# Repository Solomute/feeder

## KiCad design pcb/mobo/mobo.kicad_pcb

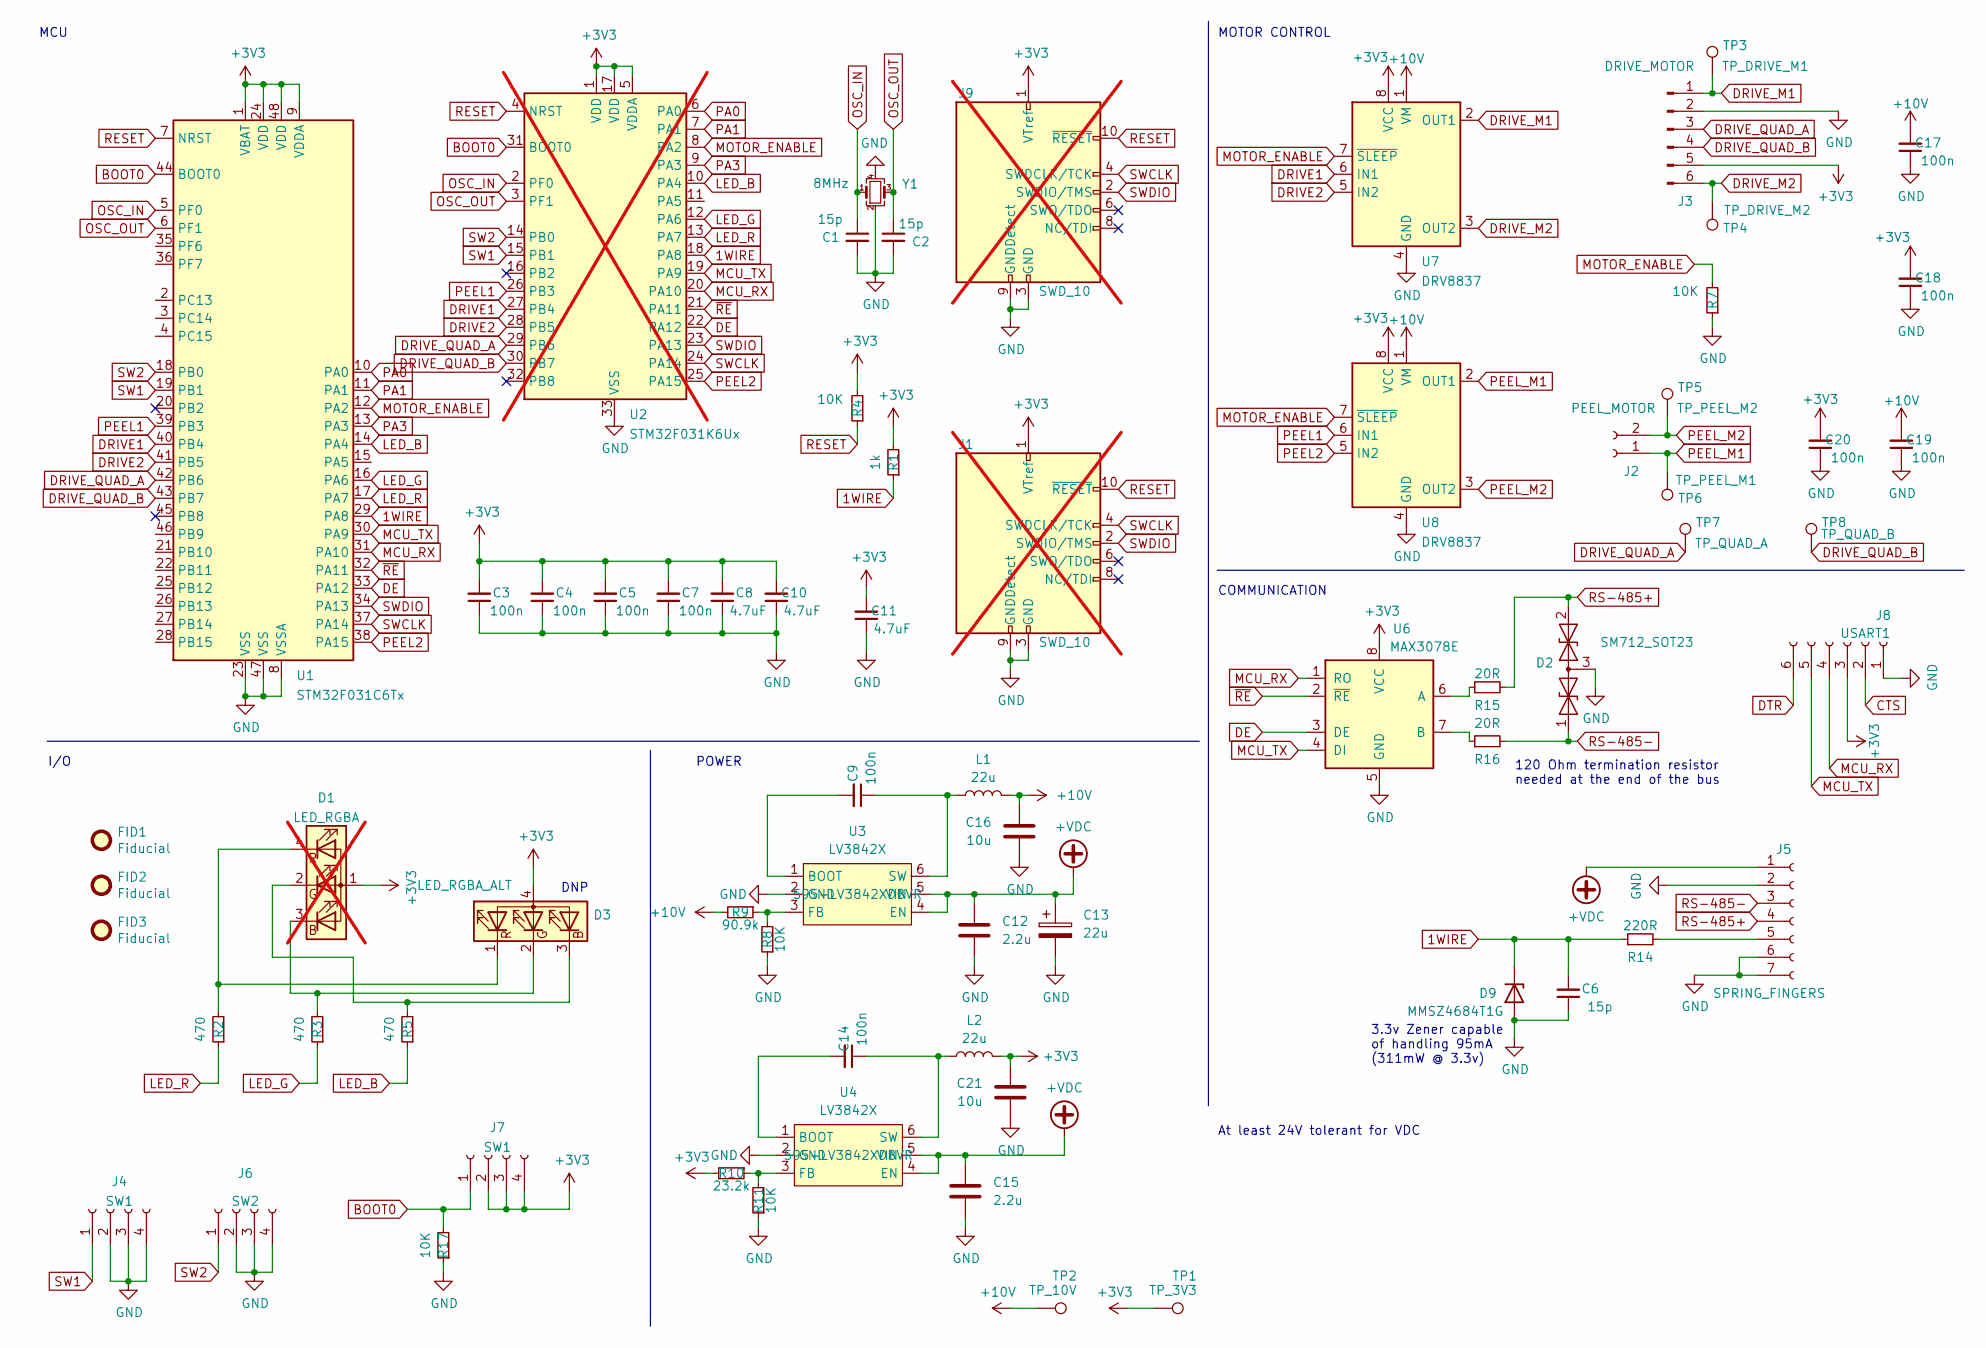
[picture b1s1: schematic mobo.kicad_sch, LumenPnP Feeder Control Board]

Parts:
C1, C2: 15p; C_0805_2012Metric; Mouser Part Number 603-CC805JRNPO9BN150; JLCPCB C1794
C3, C4, C5, C7, C9, C14, C17, C18, C19, C20: 100n; C_0805_2012Metric; Mouser Part Number 791-0805B104K500CT; JLCPCB C49678
C6: 15p; C_0805_2012Metric; Mouser Part Number 603-CC805JRNPO9BN150; JLCPCB C49678
C8, C10, C11: 4.7uF; C_0805_2012Metric; Mouser Part Number 187-CL21A475KPFNNNG; JLCPCB C49678
C12, C15: 2.2u; C_0805_2012Metric; Mouser Part Number 963-UMK212ABJ225KG-T
C13: 22u; CP_Elec_5x5.3; Mouser Part Number 80-EDK226M035A9DAA
C16, C21: 10u; C_0805_2012Metric; Mouser Part Number 187-CL21A106KOQNNNE
D1: LED_RGBA; MHS110FRGBCT; not fitted
D2: SM712_SOT23; SOT-23; Mouser Part Number 576-SM712-02HTG; LCSC C521963
D3: LED_RGBA_ALT; LED_LiteOn_LTST-C19HE1WT; Mouser Part Number 859-LTSTC19HE1WTRS1
D9: MMSZ4684T1G; D_SOD-123; Mouser Part Number 863-MMSZ4684T1G; JLCPCB MMSZ4684T1G
FID1, FID2, FID3: Fiducial; Fiducial_1mm_Mask2mm
J1: SWD_10; PinHeader_2x05_P1.27mm_Vertical_SMD; not fitted
J2: PEEL_MOTOR; Molex_PicoBlade_53261-0271_1x02-1MP_P1.25mm_Horizontal; Mouser Part Number 538-53261-0271; LCSC C2845379
J3: DRIVE_MOTOR; Molex_PicoBlade_53261-0671_1x06-1MP_P1.25mm_Horizontal; Mouser Part Number 538-53261-0671; LCSC C2845383
J4, J7: SW1; 1TS003B-1400-3500A-CT; Mouser Part Number 179-TS314635B260RASM; LCSC C319392
J5: SPRING_FINGERS; AVX-9155-005-541; Mouser Part Number 581-009155005541006
J6: SW2; 1TS003B-1400-3500A-CT; Mouser Part Number 179-TS314635B260RASM; LCSC C319392
J8: USART1; UART_FRICTION_FIT
J9: SWD_10; SWD-No-Paste; not fitted
L1, L2: 22u; L_4018; Mouser Part Number 963-NRS4018T220MDGJV
R1: 1k; R_0805_2012Metric; Mouser Part Number 708-RMCF0805FG1K00; JLCPCB C17513
R2, R3, R5: 470; R_0805_2012Metric; Mouser Part Number 603-RC0805JR-10470RL; JLCPCB C17710
R4, R7, R8, R11, R17: 10K; R_0805_2012Metric; Mouser Part Number 603-RE0805FRE0710KL; JLCPCB C17513
R9: 90.9k; R_0805_2012Metric; Mouser Part Number 71-CRCW0805-90.9K-E3
R10: 23.2k; R_0805_2012Metric; Mouser Part Number 603-RC0805FR-0723K2L
R14: 220R; R_0805_2012Metric; Mouser Part Number 667-ERJ-P06J221V
R15, R16: 20R; R_0805_2012Metric; Mouser Part Number 660-RK73H2ATTDD20R0F
TP1: TP_3V3; TestPoint_Pad_D2.0mm
TP2: TP_10V; TestPoint_Pad_D2.0mm
TP3: TP_DRIVE_M1; TestPoint_Pad_D2.0mm
TP4: TP_DRIVE_M2; TestPoint_Pad_D2.0mm
TP5: TP_PEEL_M2; TestPoint_Pad_D2.0mm
TP6: TP_PEEL_M1; TestPoint_Pad_D2.0mm
TP7: TP_QUAD_A; TestPoint_Pad_D2.0mm
TP8: TP_QUAD_B; TestPoint_Pad_D2.0mm
U1: STM32F031C6Tx; LQFP-48_7x7mm_P0.5mm; Mouser Part Number 511-STM32F031C6T6
U2: STM32F031K6Ux; QFN-32-No-Paste; not fitted
U3, U4: LV3842X; SOT-23-6; Mouser Part Number 595-LV3842XDBVR
U6: MAX3078E; SOIC-8_3.9x4.9mm_P1.27mm; Mouser Part Number 701-SP3078EEN-L/TR; JLCPCB C40031
U7, U8: DRV8837; WSON-8-1EP_2x2mm_P0.5mm_EP0.9x1.6mm; Mouser Part Number 595-DRV8837CDSGR
Y1: 8MHz; Crystal_SMD_3225-4Pin_3.2x2.5mm_HandSoldering; Mouser Part Number 520-80833B2QCVYTR; JLCPCB C253751

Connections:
1WIRE: C6.2, D9.1 (K), R1.1, R14.1, U1.29 (PA8), U2.18 (PA8)
+3V3: C3.2, C4.2, C5.2, C7.2, C8.2, C10.2, C11.2, C18.2, C20.2, C21.1, D1.1 (A), D3.4 (A), J1.1 (VTref), J3.5, J7.2, J7.3, J7.4, J8.3, J9.1 (VTref), L2.2, R1.2, R4.2, R10.2, TP1.1, U1.1 (VBAT), U1.9 (VDDA), U1.24 (VDD), U1.48 (VDD), U2.1 (VDD), U2.5 (VDDA), U2.17 (VDD), U6.8 (VCC), U7.8 (VCC), U8.8 (VCC)
+10V: C16.1, C17.2, C19.2, L1.2, R9.2, TP2.1, U7.1 (VM), U8.1 (VM)
+VDC: C12.1, C13.1, C15.1, J5.1, U3.4 (EN), U3.5 (VIN), U4.4 (EN), U4.5 (VIN)
BOOT0: J7.1, R17.2, U1.44 (BOOT0), U2.31 (BOOT0)
CTS: J8.2
DE: U1.33 (PA12), U2.22 (PA12), U6.3 (DE)
DRIVE1: U1.40 (PB4), U2.27 (PB4), U7.6 (IN1)
DRIVE2: U1.41 (PB5), U2.28 (PB5), U7.5 (IN2)
DRIVE_M1: J3.1, TP3.1, U7.2 (OUT1)
DRIVE_M2: J3.6, TP4.1, U7.3 (OUT2)
DRIVE_QUAD_A: J3.3, TP7.1, U1.42 (PB6), U2.29 (PB6)
DRIVE_QUAD_B: J3.4, TP8.1, U1.43 (PB7), U2.30 (PB7)
DTR: J8.6
GND: C1.2, C2.2, C3.1, C4.1, C5.1, C6.1, C7.1, C8.1, C10.1, C11.1, C12.2, C13.2, C15.2, C16.2, C17.1, C18.1, C19.1, C20.1, C21.2, D2.3 (common), D9.2 (A), J1.3 (GND), J1.5 (GND), J1.9 (GNDDetect), J3.2, J4.2, J4.3, J4.4, J5.2, J5.6, J5.7, J6.2, J6.3, J6.4, J8.1, J9.3 (GND), J9.5 (GND), J9.9 (GNDDetect), R7.1, R8.1, R11.1, R17.1, U1.8 (VSSA), U1.23 (VSS), U1.47 (VSS), U2.33 (VSS), U3.2 (GND), U4.2 (GND), U6.5 (GND), U7.4 (GND), U7.9 (GND), U8.4 (GND), U8.9 (GND), Y1.2, Y1.4
LED_B: R5.1, U1.14 (PA4), U2.10 (PA4)
LED_G: R3.1, U1.16 (PA6), U2.12 (PA6)
LED_R: R2.1, U1.17 (PA7), U2.13 (PA7)
MCU_RX: J8.4, U1.31 (PA10), U2.20 (PA10), U6.1 (RO)
MCU_TX: J8.5, U1.30 (PA9), U2.19 (PA9), U6.4 (DI)
MOTOR_ENABLE: R7.2, U1.12 (PA2), U2.8 (PA2), U7.7 (~SLEEP), U8.7 (~SLEEP)
unnamed: D1.3 (BK), D3.2 (GK), R3.2
unnamed: D1.2 (GK), D3.3 (BK), R5.2
unnamed: D1.4 (RK), D3.1 (RK), R2.2
unnamed: J5.5, R14.2
unnamed: C9.2, U3.1 (BOOT)
unnamed: R8.2, R9.1, U3.3 (FB)
unnamed: C9.1, L1.1, U3.6 (SW)
unnamed: C14.2, U4.1 (BOOT)
unnamed: R10.1, R11.2, U4.3 (FB)
unnamed: C14.1, L2.1, U4.6 (SW)
unnamed: R15.1, U6.6 (A)
unnamed: R16.1, U6.7 (B)
OSC_IN: C1.1, U1.5 (PF0), U2.2 (PF0), Y1.1
OSC_OUT: C2.1, U1.6 (PF1), U2.3 (PF1), Y1.3
PA0: U1.10 (PA0), U2.6 (PA0)
PA1: U1.11 (PA1), U2.7 (PA1)
PA3: U1.13 (PA3), U2.9 (PA3)
PEEL1: U1.39 (PB3), U2.26 (PB3), U8.6 (IN1)
PEEL2: U1.38 (PA15), U2.25 (PA15), U8.5 (IN2)
PEEL_M1: J2.1, TP6.1, U8.2 (OUT1)
PEEL_M2: J2.2, TP5.1, U8.3 (OUT2)
RESET: J1.10 (~RESET), J9.10 (~RESET), R4.1, U1.7 (NRST), U2.4 (NRST)
RS-485+: D2.2 (A2), J5.4, R15.2
RS-485-: D2.1 (A1), J5.3, R16.2
SW1: J4.1, U1.19 (PB1), U2.15 (PB1)
SW2: J6.1, U1.18 (PB0), U2.14 (PB0)
SWCLK: J1.4 (SWDCLK/TCK), J9.4 (SWDCLK/TCK), U1.37 (PA14), U2.24 (PA14)
SWDIO: J1.2 (SWDIO/TMS), J9.2 (SWDIO/TMS), U1.34 (PA13), U2.23 (PA13)
~RE: U1.32 (PA11), U2.21 (PA11), U6.2 (~RE)

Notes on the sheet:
I/O
DNP
COMMUNICATION
MOTOR CONTROL
POWER
3.3v Zener capable of handling 95mA (311mW @ 3.3v)
At least 24V tolerant for VDC
MCU
120 Ohm termination resistor needed at the end of the bus

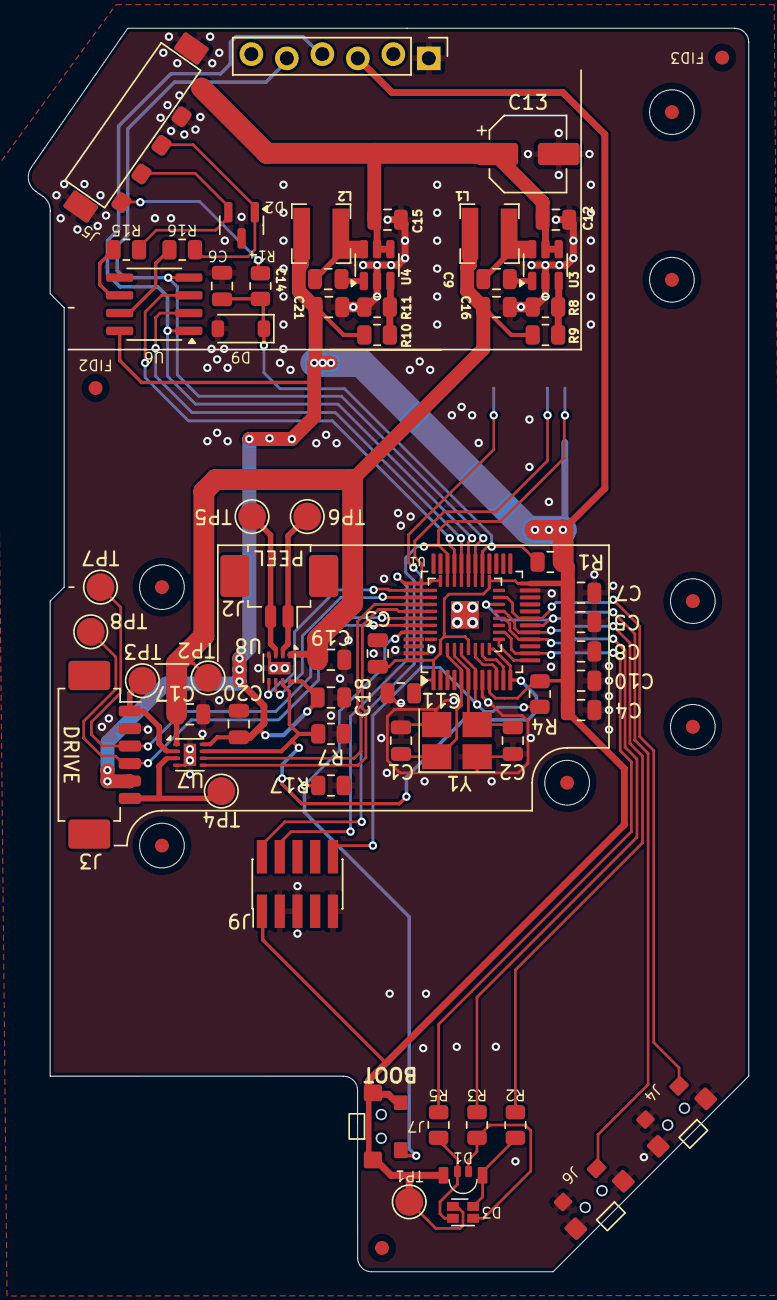
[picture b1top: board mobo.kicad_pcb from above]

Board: 2 copper layers, 51.6 x 89.0 mm, 76 parts (1 on the bottom side), 48 nets.

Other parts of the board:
H1, H2, H3, H4, H5, H6, H7: M3_Countersunk

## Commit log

2025-03-03 Power supply mangling
2025-03-03 add bom export
